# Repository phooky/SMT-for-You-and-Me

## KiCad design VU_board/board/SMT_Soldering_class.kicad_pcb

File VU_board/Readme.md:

# SMT For You and Me: VU display, Version 1

## Overview

This is a simple board with sixteen LEDs arranged in a semicircle,
that can be used as a VU meter or as a random attractive display.
It was designed for the SMT For You and Me class to introduce students
to surface mount soldering. It is based around an ATMega48 in a TQFP32
package (chosen primarily to help students practice drag soldering).

## BOM (Parts List)

BOM stands for Bill Of Materials. The BOM is a list of all the parts needed
to assemble a project. The "Reference" column of the table shows where the
part is installed on the board-- just find the same marking on your PCB!

You'll need 16 LEDs in all to fill the board, but you can select any color
combination you wish. Virtually and 0805-footprint LED will do.

Keep in mind that all of these parts are small, cheap, and easy to lose!
With the exception of the ATMega48 microcontroller, you're better off buying
extras of all the components listed. Many are actually cheaper to buy in larger
quantities-- not just per comoponent, but in total.

|Quantity |Manufacturer Part Number|Description                     |Reference|
|-----|------------------------|--------------------------------|------------------|
|1    |ATMEGA48PB-AU           |IC MCU 8BIT 4KB FLASH 32TQFP    |U1                |
|2    |CL21B104MACNNNC         |CAP CER 0.1UF 25V X7R 0805      |C1, C2            |
|1    |10118194-0001LF         |CONN RCPT USB2.0 MICRO B SMD R/A|J2                |
|1    |CL21A475KPFNNNG         |CAP CER 4.7UF 10V X5R 0805      |C4                |
|N    |LTST-C171KRKT           |LED RED CLEAR SMD               |D?                |
|N    |LTST-C171KGKT           |LED GREEN CLEAR SMD             |D?                |
|N    |LTST-C171KSKT           |LED YELLOW CLEAR CHIP SMD       |D?                |
|16   |CR0805-FX-3300ELF       |RES SMD 330 OHM 1% 1/8W 0805    |R2-17             |
|1    |CR0805-JW-472ELF        |RES SMD 4.7K OHM 5% 1/8W 0805   |R1                |
|1    |SMD4U+ME                |SMD For You and Me VU PCB       |                  |

## Assembly

Be careful to observe the correct polarity when installing the LEDs-- the cathode (negative)
end should be pointing towards the center of the board. There's a small flag with the number "1"
inside pointing to the first pin on the microcontroller; you'll find a small circle in the
corner of the chip indicating the corner that pin 1 is on. If the markings on the microcontroller
appear "upside down", you've got it right.

## Programming

The code is in the "firmware" directory and includes a Makefile for building and installing
the firmware. You may need to make some modifications to handle your setup; for instance 
change the AVRDUDE_PROGRAMMER variable to reflect the programmer you're using. There is a 
six-pin AVR ISP programming header in the lower left corner of the board. If you don't
have an AVR programmer handy, there are guides for wiring up most Arduinos to serve as a 
makeshift in-system programmer available online.

### To build and install the software:

* Hook up the ISP programmer.
* Build the firmware with "make".
* Set the fuses with "make fuses". (Fuses are an old-fashioned name for chip configuration
bits; they only need to be set once.)
* Upload the firmware with "make program".

## Using the VU meter

This section is incomplete.

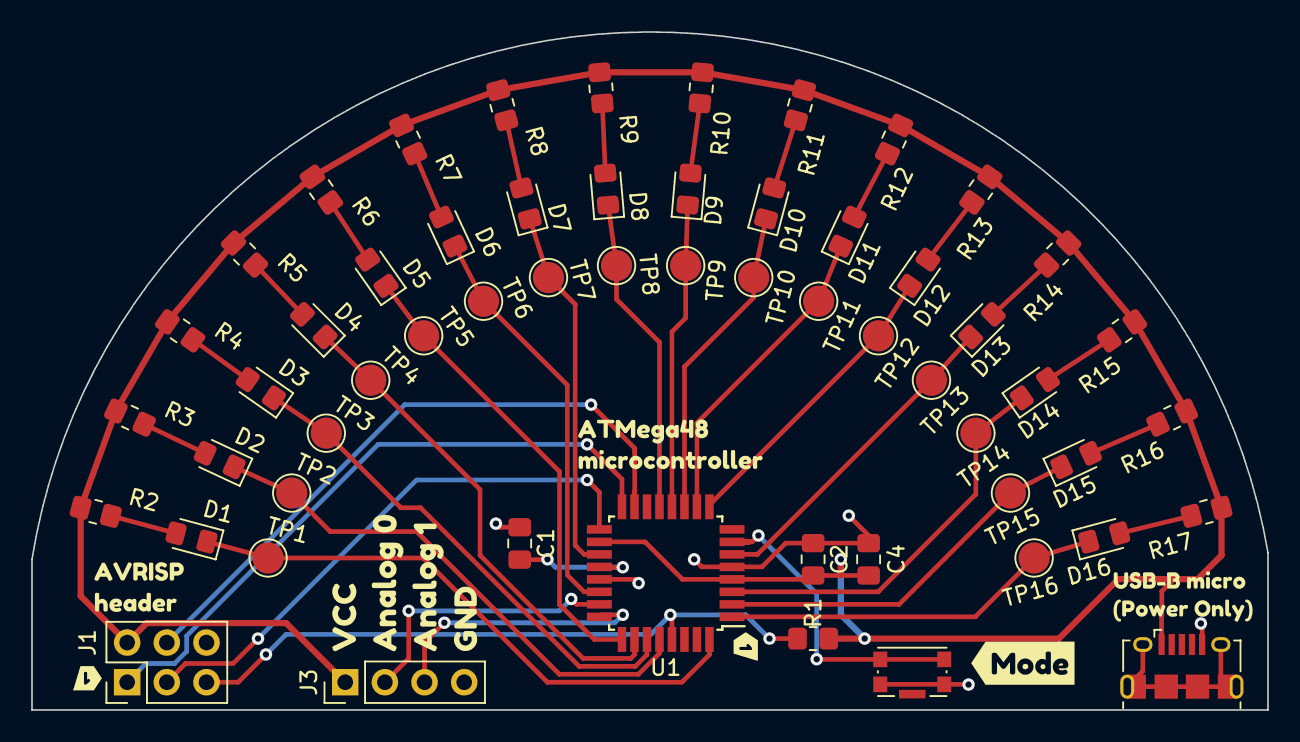
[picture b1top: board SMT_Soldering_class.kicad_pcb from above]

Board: 2 copper layers, 79.2 x 43.4 mm, 65 parts (1 on the bottom side), 42 nets.

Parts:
C1, C2: 100nF; C_0805_2012Metric_Pad1.18x1.45mm_HandSolder
C4: 4.7uF; C_0805_2012Metric_Pad1.18x1.45mm_HandSolder
D1, D2, D3, D4, D5, D6, D7, D8, D9, D10, D11, D12, D13, D14, D15, D16: LED; LED_0805_2012Metric_Pad1.15x1.40mm_HandSolder
J1: AVR-ISP-6; PinHeader_2x03_P2.54mm_Vertical
J2: USB_B_Micro; USB_Micro-B_Amphenol_10118194_Horizontal
J3: Conn_01x04; PinHeader_1x04_P2.54mm_Vertical
R1: 4.8K; R_0805_2012Metric_Pad1.20x1.40mm_HandSolder
R2, R3, R4, R5, R6, R7, R8, R9, R10, R11, R12, R13, R14, R15, R16, R17: R; R_0805_2012Metric_Pad1.20x1.40mm_HandSolder
SW1: SW_Push; SW_Push_1P1T-SH_NO_CK_KMR2xxG
TP1, TP2, TP3, TP4, TP5, TP6, TP7, TP8, TP9, TP10, TP11, TP12, TP13, TP14, TP15, TP16: TestPoint; TestPoint_Pad_D2.0mm
U1: ATmega48PB-A; TQFP-32_7x7mm_P0.8mm
kibuzzard-641A1732: G***; kibuzzard-641A1732
kibuzzard-6419EFEB: G***; kibuzzard-6419EFEB
kibuzzard-64037C19: G***; kibuzzard-64037C19
kibuzzard-64037C58: G***; kibuzzard-64037C58
kibuzzard-64037C81: G***; kibuzzard-64037C81
kibuzzard-64037CBD, kibuzzard-64037CBD#2: G***; kibuzzard-64037CBD
kibuzzard-6403760C: G***; kibuzzard-6403760C

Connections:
/ADC0: J3.2, U1.23 (PC0)
/ADC1: J3.3, U1.24 (PC1)
/LED0: D2.1 (K), TP2.1, U1.28 (PC5)
/LED1: D1.1 (K), TP1.1, U1.32 (PD2)
/LED2: D3.1 (K), TP3.1, U1.27 (PC4)
/LED3: D4.1 (K), TP4.1, U1.26 (PC3)
/LED4: D5.1 (K), TP5.1, U1.25 (PC2)
/LED5: D6.1 (K), TP6.1, U1.22 (PE3)
/LED6: D7.1 (K), TP7.1, U1.19 (PE2)
/LED7: D8.1 (K), TP8.1, U1.13 (PB1)
/LED8: D9.1 (K), TP9.1, U1.12 (PB0)
/LED9: D10.1 (K), TP10.1, U1.11 (PD7)
/LED10: D11.1 (K), TP11.1, U1.10 (PD6)
/LED11: D12.1 (K), TP12.1, U1.9 (PD5)
/LED12: D13.1 (K), TP13.1, U1.6 (PE1)
/LED13: D14.1 (K), TP14.1, U1.3 (PE0)
/LED14: D15.1 (K), TP15.1, U1.2 (PD4)
/LED15: D16.1 (K), TP16.1, U1.1 (PD3)
/RESET: J1.5 (~RST), R1.1, U1.29 (~RESET/PC6)
/SCK: J1.3 (SCK), U1.17 (PB5)
/SDI: J1.1 (MISO), U1.16 (PB4)
/SDO: J1.4 (MOSI), U1.15 (PB3)
GND: C1.1, C2.1, C4.2, J1.6 (GND), J2.5 (GND), J3.4, SW1.1, U1.5 (GND), U1.21 (GND)
unnamed: C1.2, U1.20 (AREF)
unnamed: D1.2 (A), R2.2
unnamed: D2.2 (A), R3.2
unnamed: D3.2 (A), R4.2
unnamed: D4.2 (A), R5.2
unnamed: D5.2 (A), R6.2
unnamed: D6.2 (A), R7.2
unnamed: D7.2 (A), R8.2
unnamed: D8.2 (A), R9.2
unnamed: D9.2 (A), R10.2
unnamed: D10.2 (A), R11.2
unnamed: D11.2 (A), R12.2
unnamed: D12.2 (A), R13.2
unnamed: D13.2 (A), R14.2
unnamed: D14.2 (A), R15.2
unnamed: D15.2 (A), R16.2
unnamed: D16.2 (A), R17.2
unnamed: SW1.2, U1.7 (XTAL1/PB6)
VCC: C2.2, C4.1, J1.2 (VCC), J2.1 (VBUS), J3.1, R1.2, R2.1, R3.1, R4.1, R5.1, R6.1, R7.1, R8.1, R9.1, R10.1, R11.1, R12.1, R13.1, R14.1, R15.1, R16.1, R17.1, U1.4 (VCC), U1.18 (AVCC)

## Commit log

2023-03-03 initial checkin w/ crystal
2023-03-05 version 1.0, march 2023, ready to fab
2023-03-16 reorganizing repository, adding firmware
2023-03-16 reorg continues
2023-03-16 Adding some documentation.
2023-03-22 added switch to PCB adding modes to firmware (for old version)
2023-04-08 adding code to handle button on v2
